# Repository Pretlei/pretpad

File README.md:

# Pretpad
Pretpad is a macropad for personal use. It has four keys, a rotary encoder with a switch, an oled screen, two LEDs, and uses QMK firmware.
Keys opens browser, puts laptop to sleep, pause/play song, and skips song on Spotify. Rotary encoder controls volume and its switch mutes all audio. OLED Screen displays time since the macropad has been turned on, which usually correlates to time on screen. 
## CAD

I used 4 M3 bolts and nuts in my CAD. I don't have a soldering iron, but I hope to get one so I can use heatset inserts! It has two seperate printed pieces, a top and a bottom. Made in Fusion360.
## PCB
Schematic:

PCB:

## Firmware
Uses QMK firmware! Purpose of each part is outlined in the initial description. I'll change my firmware in the future if I find some features redundant.
## BOM:
- 4x Cherry MX Switches
- 4x DSA Keycaps
- 4x M3x5x4 Heatset inserts
- 4x M3x16mm SHCS Bolts
- 2x WS2812B LEDs
- 1x 0.91" 128x32 OLED Display
- 1x EC11 Rotary Encoder
- 1x XIAO RP2040
- 1x Case (2 printed parts)
- 1x Custom PCB

## Pictures of Work In Progress:

Project was left unfinished due to medical reasons.

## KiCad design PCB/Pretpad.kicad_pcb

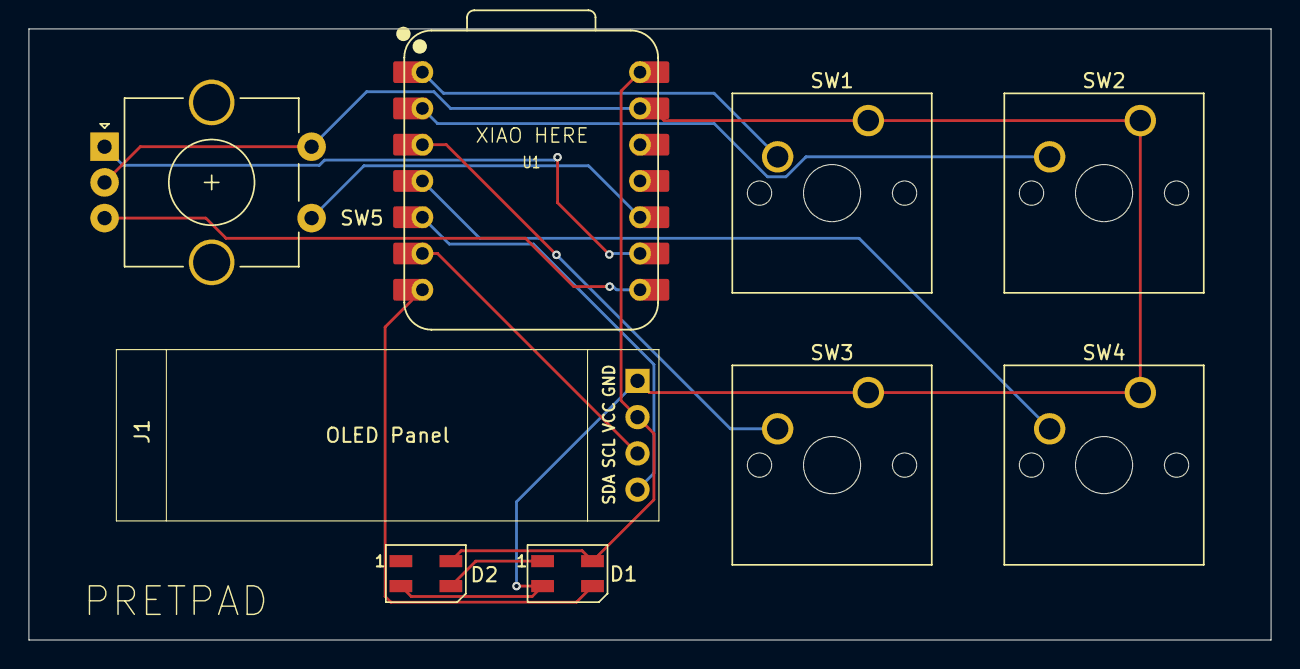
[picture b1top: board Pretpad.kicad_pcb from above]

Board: 2 copper layers, 87.0 x 42.8 mm, 9 parts (0 on the bottom side), 13 nets.

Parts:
D1, D2: SK6812MINI; LED_SK6812MINI_PLCC4_3.5x3.5mm_P1.75mm
J1: OLED_DISPLAY; SSD1306-0.91-OLED-4pin-128x32-footprint
SW1, SW2, SW3, SW4: SW_Push; SW_Cherry_MX_1.00u_PCB
SW5: RotaryEncoder_Switch; RotaryEncoder_Alps_EC11E-Switch_Vertical_H20mm_CircularMoun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
U1: XIAO-RP2040-DIP

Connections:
+5V: D1.4 (VDD), D2.4 (VDD), J1.2, U1.14 (VBUS)
GND: D1.2 (VSS), D2.2 (VSS), J1.1, SW1.1, SW2.1, SW3.1, SW4.1, SW5.C, SW5.S2, U1.13 (GND)
unnamed: D1.3 (DIN), U1.7 (GPIO0/TX)
unnamed: D1.1 (DOUT), D2.3 (DIN)
unnamed: J1.4, U1.5 (GPIO6/SDA)
unnamed: J1.3, U1.6 (GPIO7/SCL)
unnamed: SW5.B, U1.8 (GPIO1/RX)
unnamed: SW5.A, U1.9 (GPIO2/SCK)
unnamed: SW5.S1, U1.10 (GPIO4/MISO)
unnamed: SW1.2, U1.1 (GPIO26/ADC0/A0)
unnamed: SW2.2, U1.2 (GPIO27/ADC1/A1)
unnamed: SW3.2, U1.3 (GPIO28/ADC2/A2)
unnamed: SW4.2, U1.4 (GPIO29/ADC3/A3)

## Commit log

2026-03-31 Document project status in README
